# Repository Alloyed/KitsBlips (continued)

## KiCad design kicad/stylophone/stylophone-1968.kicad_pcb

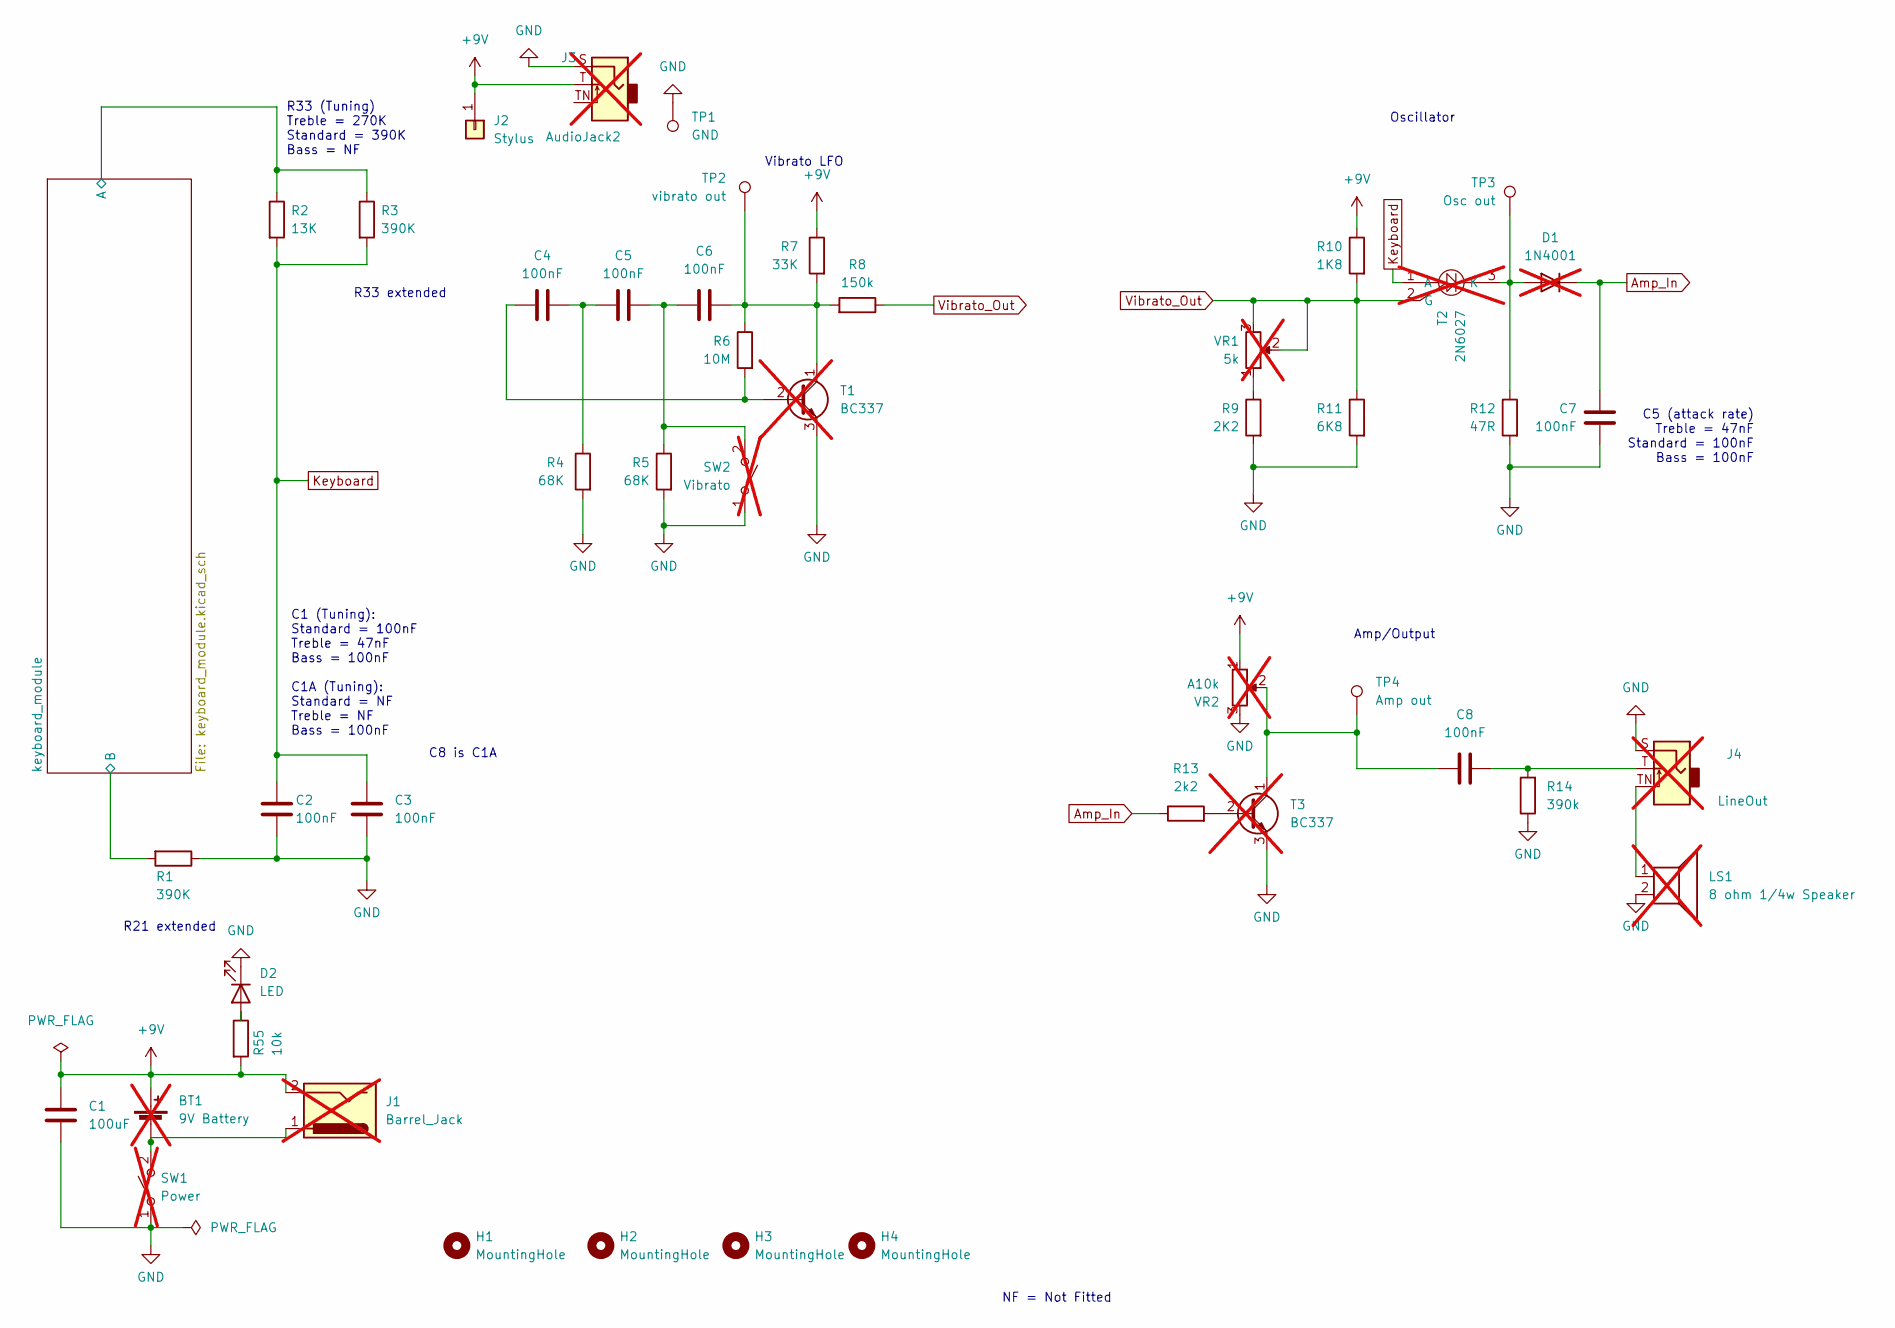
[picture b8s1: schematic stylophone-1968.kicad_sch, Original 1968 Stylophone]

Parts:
BT1: 9V Battery; BatteryHolder_Eagle_12BH611-GR; not fitted
C1: 100uF; C_1206_3216Metric_Pad1.33x1.80mm_HandSolder
C2, C3, C4, C5, C6, C7, C8: 100nF; C_0603_1608Metric_Pad1.08x0.95mm_HandSolder
D1: 1N4001; D_DO-41_SOD81_P10.16mm_Horizontal; not fitted
D2: LED; LED_D3.0mm
H1, H2, H3, H4: MountingHole; MountingHole_3.2mm_M3
J1: Barrel_Jack; BarrelJack_CUI_PJ-063AH_Horizontal; not fitted
J2: Stylus; TestPoint_Pad_D4.0mm
J3: AudioJack2; Jack_3.5mm_QingPu_WQP-PJ398SM_Vertical_CircularHoles; Part Number WQP-WQP518MA; not fitted
J4: LineOut; Jack_3.5mm_QingPu_WQP-PJ398SM_Vertical_CircularHoles; Part Number WQP-WQP518MA; not fitted
LS1: 8 ohm 1/4w Speaker; mouser_speaker; not fitted
R1, R3: 390K; R_0603_1608Metric_Pad0.98x0.95mm_HandSolder
R2: 13K; R_0603_1608Metric_Pad0.98x0.95mm_HandSolder
R4, R5: 68K; R_0603_1608Metric_Pad0.98x0.95mm_HandSolder
R6: 10M; R_0603_1608Metric_Pad0.98x0.95mm_HandSolder
R7: 33K; R_0603_1608Metric_Pad0.98x0.95mm_HandSolder
R8: 150k; R_0603_1608Metric_Pad0.98x0.95mm_HandSolder
R9: 2K2; R_0603_1608Metric_Pad0.98x0.95mm_HandSolder
R10: 1K8; R_0603_1608Metric_Pad0.98x0.95mm_HandSolder
R11: 6K8; R_0603_1608Metric_Pad0.98x0.95mm_HandSolder
R12: 47R; R_0603_1608Metric_Pad0.98x0.95mm_HandSolder
R13: 2k2; R_0603_1608Metric_Pad0.98x0.95mm_HandSolder
R14: 390k; R_0603_1608Metric_Pad0.98x0.95mm_HandSolder
R55: 10k; R_0603_1608Metric_Pad0.98x0.95mm_HandSolder
SW1: Power; SLW-1277744-3A-N-D; not fitted
SW2: Vibrato; SLW-1277744-3A-N-D; not fitted
T1, T3: BC337; TO-92_HandSolder; not fitted
T2: 2N6027; TO-92_HandSolder; not fitted
TP1: GND; TestPoint_Pad_3.0x3.0mm
TP2: vibrato out; TestPoint_Pad_3.0x3.0mm
TP3: Osc out; TestPoint_Pad_3.0x3.0mm
TP4: Amp out; TestPoint_Pad_3.0x3.0mm
VR1: 5k; Potentiometer_Bourns_3266Y_Vertical; not fitted
VR2: A10k; RD901F4015R1B10K00DL1; not fitted

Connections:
+9V: BT1.1 (+), C1.1, J1.2, J2.1, J3.T, R7.1, R10.1, R55.2, VR2.1
/keyboard_module/A1: R2.1, R3.1; also elsewhere on the board
/keyboard_module/B11: R1.2; also elsewhere on the board
Amp_In: C7.1, D1.1 (K), R13.1
GND: C1.2, C2.2, C3.2, C7.2, D2.1 (K), J3.S, J4.S, LS1.2, R1.1, R4.2, R5.2, R9.2, R11.2, R12.2, R14.1, SW1.1 (A), SW2.1 (A), T1.3 (E), T3.3 (E), TP1.1, VR2.3
Keyboard: C2.1, C3.1, R2.2, R3.2, T2.1 (A)
unnamed: BT1.2 (-), J1.1, SW1.2 (B)
unnamed: C4.1, C5.2, R4.1
unnamed: C8.2, J4.T, R14.2
unnamed: D1.2 (A), R12.1, T2.3 (K), TP3.1
unnamed: D2.2 (A), R55.1
unnamed: J4.TN, LS1.1
unnamed: R9.1, VR1.1
unnamed: C5.1, C6.2, R5.1, SW2.2 (B)
unnamed: C4.2, R6.2, T1.2 (B)
unnamed: C6.1, R6.1, R7.2, R8.2, T1.1 (C), TP2.1
unnamed: R13.2, T3.2 (B)
unnamed: C8.1, T3.1 (C), TP4.1, VR2.2
Vibrato_Out: R8.1, R10.2, R11.1, T2.2 (G), VR1.2, VR1.3

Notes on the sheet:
C1 (Tuning): Standard = 100nF Treble = 47nF Bass = 100nF C1A (Tuning): Standard = NF Treble = NF Bass = 100nF
C8 is C1A
Oscillator
R33 extended
R33 (Tuning) Treble = 270K Standard = 390K Bass = NF
R21 extended
Amp/Output
Vibrato LFO
NF = Not Fitted
C5 (attack rate) Treble = 47nF Standard = 100nF Bass = 100nF

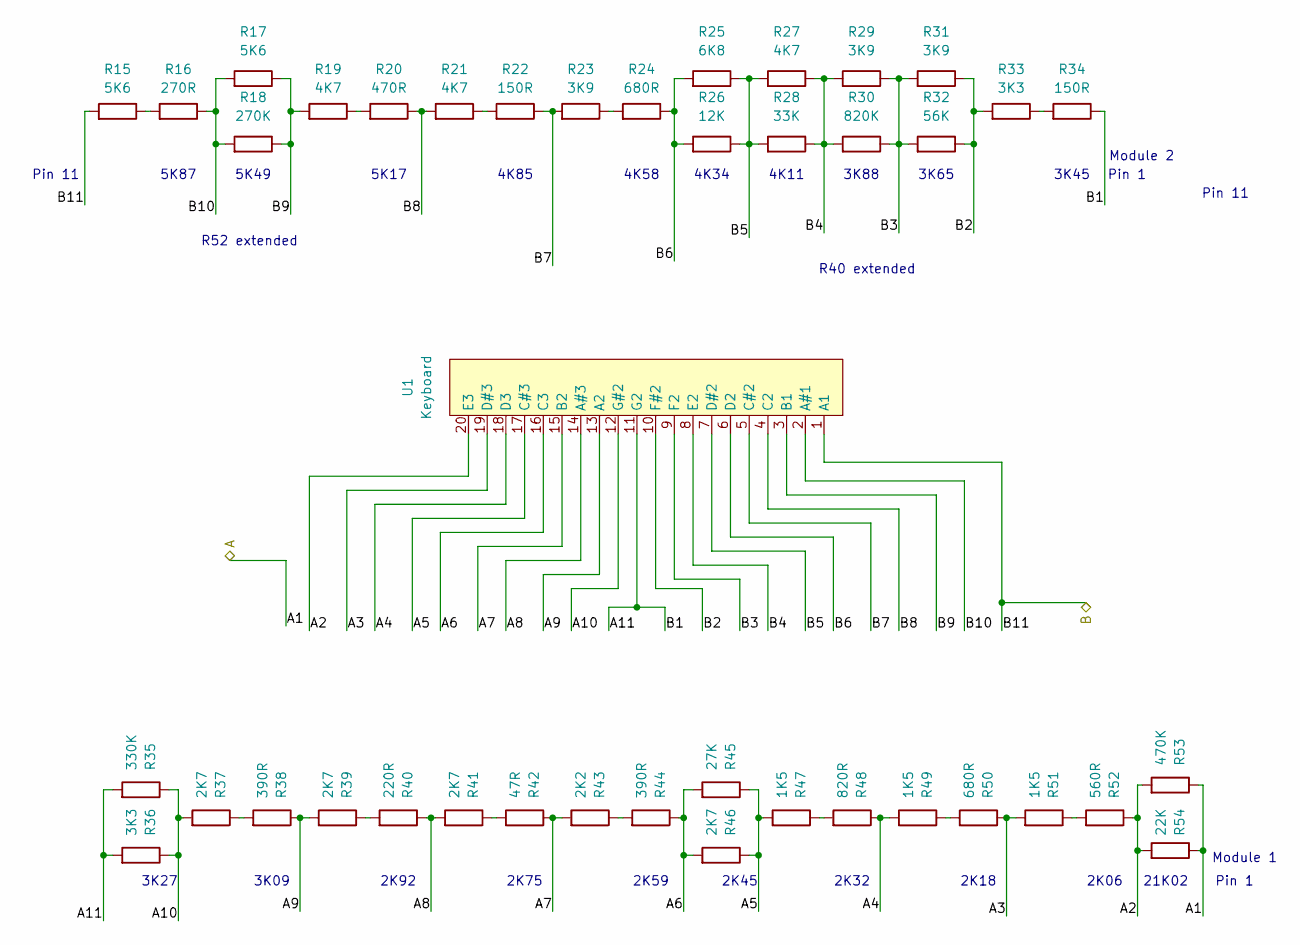
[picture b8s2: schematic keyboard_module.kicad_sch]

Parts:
R15, R17: 5K6; R_0603_1608Metric_Pad0.98x0.95mm_HandSolder
R16: 270R; R_0603_1608Metric_Pad0.98x0.95mm_HandSolder
R18: 270K; R_0603_1608Metric_Pad0.98x0.95mm_HandSolder
R19, R21, R27: 4K7; R_0603_1608Metric_Pad0.98x0.95mm_HandSolder
R20: 470R; R_0603_1608Metric_Pad0.98x0.95mm_HandSolder
R22, R34: 150R; R_0603_1608Metric_Pad0.98x0.95mm_HandSolder
R23, R29, R31: 3K9; R_0603_1608Metric_Pad0.98x0.95mm_HandSolder
R24, R50: 680R; R_0603_1608Metric_Pad0.98x0.95mm_HandSolder
R25: 6K8; R_0603_1608Metric_Pad0.98x0.95mm_HandSolder
R26: 12K; R_0603_1608Metric_Pad0.98x0.95mm_HandSolder
R28: 33K; R_0603_1608Metric_Pad0.98x0.95mm_HandSolder
R30: 820K; R_0603_1608Metric_Pad0.98x0.95mm_HandSolder
R32: 56K; R_0603_1608Metric_Pad0.98x0.95mm_HandSolder
R33, R36: 3K3; R_0603_1608Metric_Pad0.98x0.95mm_HandSolder
R35: 330K; R_0603_1608Metric_Pad0.98x0.95mm_HandSolder
R37, R39, R41, R46: 2K7; R_0603_1608Metric_Pad0.98x0.95mm_HandSolder
R38, R44: 390R; R_0603_1608Metric_Pad0.98x0.95mm_HandSolder
R40: 220R; R_0603_1608Metric_Pad0.98x0.95mm_HandSolder
R42: 47R; R_0603_1608Metric_Pad0.98x0.95mm_HandSolder
R43: 2K2; R_0603_1608Metric_Pad0.98x0.95mm_HandSolder
R45: 27K; R_0603_1608Metric_Pad0.98x0.95mm_HandSolder
R47, R49, R51: 1K5; R_0603_1608Metric_Pad0.98x0.95mm_HandSolder
R48: 820R; R_0603_1608Metric_Pad0.98x0.95mm_HandSolder
R52: 560R; R_0603_1608Metric_Pad0.98x0.95mm_HandSolder
R53: 470K; R_0603_1608Metric_Pad0.98x0.95mm_HandSolder
R54: 22K; R_0603_1608Metric_Pad0.98x0.95mm_HandSolder
U1: Keyboard; stylophone-keyboard

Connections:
/keyboard_module/A1: R53.1, R54.1; also elsewhere on the board
/keyboard_module/A2: R52.1, R53.2, R54.2, U1.20 (E3)
/keyboard_module/A3: R50.1, R51.2, U1.19 (D#3)
/keyboard_module/A4: R48.1, R49.2, U1.18 (D3)
/keyboard_module/A5: R45.1, R46.1, R47.2, U1.17 (C#3)
/keyboard_module/A6: R44.1, R45.2, R46.2, U1.16 (C3)
/keyboard_module/A7: R42.1, R43.2, U1.15 (B2)
/keyboard_module/A8: R40.1, R41.2, U1.14 (A#3)
/keyboard_module/A9: R38.1, R39.2, U1.13 (A2)
/keyboard_module/A10: R35.1, R36.1, R37.2, U1.12 (G#2)
/keyboard_module/A11: R34.1, R35.2, R36.2, U1.11 (G2)
/keyboard_module/B2: R31.1, R32.1, R33.2, U1.10 (F#2)
/keyboard_module/B3: R29.1, R30.1, R31.2, R32.2, U1.9 (F2)
/keyboard_module/B4: R27.1, R28.1, R29.2, R30.2, U1.8 (E2)
/keyboard_module/B5: R25.1, R26.1, R27.2, R28.2, U1.7 (D#2)
/keyboard_module/B6: R24.1, R25.2, R26.2, U1.6 (D2)
/keyboard_module/B7: R22.1, R23.2, U1.5 (C#2)
/keyboard_module/B8: R20.1, R21.2, U1.4 (C2)
/keyboard_module/B9: R17.1, R18.1, R19.2, U1.3 (B1)
/keyboard_module/B10: R16.1, R17.2, R18.2, U1.2 (A#1)
/keyboard_module/B11: R15.2, U1.1 (A1); also elsewhere on the board
unnamed: R15.1, R16.2
unnamed: R19.1, R20.2
unnamed: R21.1, R22.2
unnamed: R23.1, R24.2
unnamed: R33.1, R34.2
unnamed: R37.1, R38.2
unnamed: R39.1, R40.2
unnamed: R41.1, R42.2
unnamed: R43.1, R44.2
unnamed: R47.1, R48.2
unnamed: R49.1, R50.2
unnamed: R51.1, R52.2

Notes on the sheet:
Module 1
4K85
3K65
2K75
R40 extended
5K49
R52 extended
5K17
2K59
Pin 11
2K32
Module 2
Pin 1
3K88
3K45
2K92
4K11
2K45
3K09
2K06
4K58
5K87
4K34
2K18
21K02
3K27

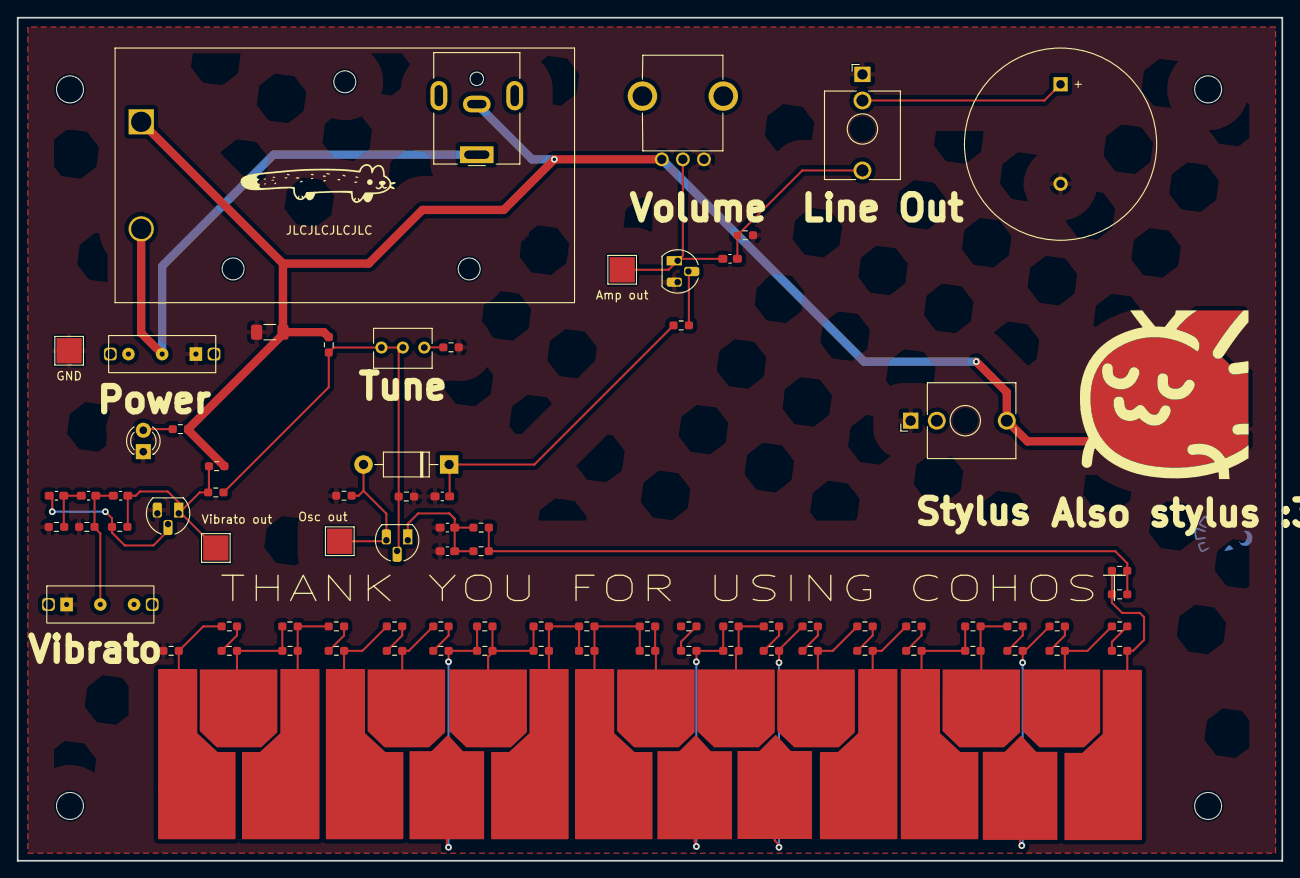
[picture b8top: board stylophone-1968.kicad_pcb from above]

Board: 2 copper layers, 150.0 x 100.0 mm, 87 parts (0 on the bottom side), 50 nets.

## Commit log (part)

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2025-05-20 use static libsdl
2025-05-21 Switch to clapfirst script
2025-05-21 cmake shuffling
2025-05-21 Rewrite plugin.cpp to avoid designated initializers
2025-05-21 more windows fixes
2025-05-21 minor CI speedup by disabling SDL subsystems
2025-05-22 ok that didn't work, try this thing instead
2025-05-23 one of these days
2025-05-24 Fix VCVRack on linux
2025-05-25 Clap: Switch to single-project structure
2025-05-31 build fix
2025-05-31 Start work on effect plugin template
2025-05-31 Stateful extensions, parameters support
2025-06-01 More work to get the parameters extension up to par
2025-06-01 respond to activate/reset events
2025-06-01 fixess from bitwig testing
2025-06-01 Base plugin header cleanup
2025-06-01 Create instrumentPlugin type
2025-06-01 Changes to pass validator testing
2025-06-01 fix clang-tidy warnings
2025-06-01 Create build artifacts for clap plugins
2025-06-01 new clap plugin: sines (test case for instruments)
2025-06-02 oh my god im silly (anyways plugins have sound now)
2025-06-02 gui work
2025-06-04 misc non-gui fixes
2025-06-04 ough
2025-06-05 an alternative to strcpy that's actually portable
2025-06-05 fix windows
2025-06-07 cleanup
2025-06-07 runtime support for multiple apis (for wayland, mostly)
2025-06-07 windows fixes
2025-06-07 SDL multiple-window support
2025-06-07 whoops didn't mean to delete that
2025-06-07 2-way gesture sync
2025-06-07 cleanup, host support logging
2025-06-07 extension support matrix, use SetTimer() on windows (because many hosts don't support the timer api :/)
2025-06-08 support enum parameters. support parameters to text
2025-06-08 cleanup again
2025-06-08 split imgui and sdl into two subclasses
2025-06-08 clap support library now has a name! clapeze (like trapeze, get it)
2025-06-08 event more cleanup
2025-06-08 big refactor: move all processing-related methods and state into "Processor" objects.
2025-06-08 voice allocation
2025-06-13 bweh
2025-06-14 vtable-based polymorphic parameters
2025-06-14 update parameter usage to avoid GetRaw()
2025-06-14 only look for/compile SDL3 if used
2025-06-14 don't define imgui methods if gui not enabled
2025-06-14 oh, duh
2025-06-14 yoloing out a direct translation of crunch
2025-06-14 windows things
2025-06-15 Trying different polyblep algorithm
2025-06-15 smaller things
2025-06-17 CLAP module support (I would call this category or group instead but what can you do)
2025-06-17 tighten up waning options
2025-06-19 auto-format
2025-06-21 initial knob support
2025-06-21 namespacing, some mesh copy-paste
2025-06-22 3d scene exploration
2025-06-22 wip: switch to glad
2025-06-22 Fix clap (by removing gui support)
2025-06-23 ...i still need to play deltarune
2025-06-24 accidentally hyperfocused on building signals from scratch whoops
2025-06-24 it compiles :)
2025-06-27 fun with untested dsp code :)
2025-06-29 more gfx, created stub for sprite batches
2025-06-29 name the thing what it is
2025-07-03 switchting to magnum graphics lib
2025-07-03 scene from sample player ported
2025-07-04 header cleanup
2025-07-04 actual test code :0
2025-07-04 ai slop cleanup (watchout!)
2025-07-04 windows testing
2025-07-05 clap fixes
2025-07-05 disabling clap macos for now
2025-07-08 corrade logging banished, kitgui::log in
2025-07-08 proper window resizing
2025-07-08 /shrug
2025-07-12 re-enable debug imgui support
2025-07-13 platform timer
2025-07-20 move clapeze into a top-level subdirectory
2025-07-20 compile windows again
2025-07-21 big refactor: rename Exts to "features", adopt "TObject" prefix for template params
2025-07-21 update clap plugins to use param traits
2025-07-22 move more param configuration into the trait
2025-07-22 clang-tidy
2025-07-22 clang-tidy changes for kitdsp
2025-08-03 more cleanup
2025-08-05 fix compiler warnings
2025-08-05 re-enable clap macos
2025-08-08 remove GLAD. add AudioFile (for wav file reading/writing)
2025-08-08 Fixup test for chorus (yeah it's broken...)
2025-08-08 chorus works now :)
2025-08-09 move more tests to AudioFile
2025-08-09 playing with an eventide h910 algorithm (this isn't a grain player, whoops~~~)
2025-08-10 actually name the harmonizer what it is
2025-08-15 frequency shifter works :0
2025-08-15 fix windows builds
2025-08-24 move sdl implementation into a impl class
2025-08-24 inline old platform code into the one SDL file to rule them all
2025-08-24 update clap wrapper for new gui api
2025-08-24 rendering.... works....?
2025-08-24 don't include SDL3 when we don't need to
2025-08-25 wide string shenanigans
2025-08-25 crunch gui seems to work!
2025-08-25 okkkk one more
2025-08-28 Add skeletons for new daw plugins
2025-08-29 ok what if i added every plugin all at once
2025-08-29 small sync
2025-08-30 fill out each plugin with debug gui
2025-08-31 linux fixups
2025-08-31 fixups 2
2025-08-31 fixups 3
2025-09-04 shuffling things around for no particular reason
2025-09-04 Split out extensions and features for good: now each feature can register as many extensions as it likes (or none!)
2025-09-06 Add skeleton of preset support
2025-09-07 feature frenzy
2025-09-16 tmp: working out affinity designer -> vcv rack pipeline
2025-09-16 I forgor
2025-09-17 fix macosx build?
2025-09-17 MacOS fix, switch to libfmt instead of std::format
2025-09-17 use builtin fmt library. silly.
2025-09-17 fix windows pls :pleading:
2025-09-28 windows fix (again)
2025-09-28 cache is dependent on repo state, duh
2025-09-28 Add cocoa stub implementation
2025-09-28 cmake: try out composite actions
2025-09-28 fix macos :)
2025-09-28 more ci cleanup
2025-12-28 ummmm, i don't remember :(
2025-12-31 use automatic entry point in actual clap plugins
2025-12-31 3d still needs time to bake
2025-12-31 kitgui: file loading infrastructure so i can skippo the C++ embedded thing
2025-12-31 entry point fixes
2025-12-31 more buildfix
2025-12-31 add more examples
2025-12-31 fix 3d scene loading for actual
2026-01-04 Fix annoying ParamTraits template bug
    ParamTraits<Param1::myId> and ParamTraits<Param2::myId> both eventually
    resolve to ParamTraits<1>, even if the params are enum classes. to fix,
    we'll manually pass in the full params enum as a qualifier
2026-01-04 plugin entry callsite simplification
2026-01-05 Expose gfx/Scene as a non dom type/api
2026-01-05 kitskeys panel first pass, CI fixes
2026-01-05 yes i know im using a nonstandard extension
2026-01-06 robustify linux/x11 implementation (so i can hunt down the issue a bit better)
2026-01-06 keysynth parameter cleanup
2026-01-06 combined voice pool; modulation storage
2026-01-06 Fix linux gui!!!!
2026-01-07 redo file loader plumbing. (untested but this should mean physfs in gui will Just Work)
2026-01-07 Fix context cleanup: app should always be destroyed before rest of context
2026-01-07 fix ci maybe
2026-01-07 Fix embarassing C++ bugs
2026-01-07 ok this one is more embarassing for apple
2026-01-08 lotsa small stuff
2026-01-09 lotsa big stuff
2026-01-10 fix mac?
2026-01-11 big documentation pass
2026-01-11 add pugl to sdk dir
2026-01-12 Fully replace physfs with miniz
2026-01-12 update docs
2026-01-13 pugl, big implementation pass
2026-01-13 pugl bugfixes
2026-01-14 fix debug ui bug
2026-01-14 ci fixes
2026-01-14 mac fixes
2026-01-14 oops that makes sense
2026-01-16 wrenching on cmake a bit
2026-01-16 format_to_n doesn't write the terminator :(
2026-01-17 optional sentry.io crash reporting
2026-01-18 sentry doubled the build size, turning off for now
2026-01-18 also mac
2026-01-22 rename clap folder to daw
2026-01-23 unit tests, woah
2026-01-24 mock host for convenient testing
2026-01-24 docs pass
2026-01-24 new experiment: alternate parameter implementations
2026-01-24 adopt new parameter system in clapeze
2026-01-24 upgrade daw to use new parameter system too
2026-01-24 constraints and concepts (scary!)
2026-01-24 remove vestigial clapeze::params::Id type
2026-01-24 more and better integration testing
2026-01-25 exploring toml serialization
2026-01-25 iostreams for clap streams
2026-01-25 perf and time tracking
2026-01-25 Support UI scale on SDL backend, fixes X11 being tiny
2026-01-26 stuff
2026-01-28 update libdaisy
2026-01-28 update other submodules
2026-01-28 update vcvrack sdk
2026-01-28 add gltfpack and basisu for asset packing
2026-01-28 daisy fix
2026-01-28 verbose logs
2026-01-28 silly mistake: .gitignore ignored the binaries :p
2026-01-28 initial setup script
2026-01-28 add sentry to ci
2026-01-29 AI statement (gee i wonder what prompted this)
2026-01-30 whoops unitialized memory!!
2026-01-31 gui backend hardening
2026-01-31 actually working knobs (WOAH)
2026-02-01 bugfix pass: fix dangling pointers resulting from not realizing the host is allowed to pass multiple host pointers back, and a multi-window imgui thing
2026-02-03 KitsKeys Chord mode
2026-02-03 fixed polyphonic voice stealing algo
2026-02-03 lots of poorly considered stuff
2026-02-03 silly mistake: putting windows inside of windows are we
2026-02-03 toggle switches
2026-02-04 ui cleanup
2026-02-07 better oversampling
2026-02-07 misc cleanup
2026-02-08 nvm ill bring back lfo sync later, more issues than expected
2026-02-08 new kitskeys front panel
2026-02-08 LFO sync + LFO out(for light)
2026-02-08 scene hierarchy debug view, bounding-box knobs
2026-02-08 add sentry-cli to cmake
2026-02-09 x11 highdpi hack
2026-02-10 Big params refactor (split up FillInformation, add key, deemphasize module as it's relatively unused)
2026-02-11 key followup, updating callsites and such
2026-02-11 warning silencer
2026-02-13 big filename refactor
2026-02-13 file renaming: group audio stuff together under "processor" folder
2026-02-13 include clapeze with system headers when external to it
2026-02-14 un-templatify params handle storage
2026-02-14 custom casts
2026-02-15 exposing ambient brightness
2026-02-15 you should be pulling in assets if you use kitgui
2026-02-15 pawing at preset browser
2026-02-15 preset work
2026-02-16 remove glob, use no-compression mode for zip bundle
2026-02-16 ok nvm i'll write my own zip-creator
2026-02-20 wip: post processing pass
2026-02-21 emissive blur effect!
2026-02-21 more light tricks
2026-02-21 whoops
2026-02-22 new model
2026-02-22 toggle off basis for now
2026-02-22 glb test assets
2026-02-23 asset
2026-02-23 emissive effect tweaking
2026-02-27 wawa
2026-02-28 Fix #29 and #30
2026-03-03 fix #32: don't try to set the current dpi awareness setting, you and the host may disagree!
2026-03-06 KitsBlips DAW version 0.1.0
2026-04-13 snapshot testing... maybe
2026-04-13 rename ProcessorHandle to AudioHandle
2026-04-13 snapshots!
2026-04-21 implement it
2026-04-22 going psola-mode
2026-04-26 more pitch shift groundwork
2026-05-02 ...i forget
2026-05-03 disperser (?) ...i may have screwed up the math i think
2026-05-07 disperser work, crossover filter, simd vector (experimental)
2026-05-07 filter plugin
2026-05-07 transfer functions (for later)
2026-05-08 fix a few kitsblips bugs
2026-05-09 filter fixies
2026-05-09 buildfix
2026-05-17 starting on layersynth
2026-05-17 added "some stuff"
2026-05-18 swagify
2026-05-20 3 band equalizer
2026-05-22 crazy work (normal work)
2026-05-22 more wiring
2026-05-22 slowly running out of awake juice
2026-05-23 event based parameters?
2026-05-23 nativefiledialog integration
2026-05-23 more things working
2026-05-23 weewa
2026-05-23 ok this is mostly crash free now i think
2026-05-23 more fixies
2026-05-23 ci upgrade
2026-05-24 fix parameter queue getting overfull as a result of initialization
2026-05-24 polyphonic modulation (maybe)
2026-05-24 switch to drwav/drflac for sample loading (that means flac support, yipee)
2026-05-24 fixing again
2026-05-24 killing sentry
2026-05-24 modulation works now
2026-05-25 Jam Session :)
2026-05-31 sample player debugging
2026-05-31 update snapshots
2026-06-02 fix everything, all at once (again, whoops)
2026-06-04 sample player polish
2026-06-04 more sample player api polish
2026-06-05 add implot
2026-06-05 dx7 envelope (probably better to name multistage?)
2026-06-05 fantsy sample editor
2026-06-06 lofi sample pre-processing
2026-06-07 unnecessarily big cl
2026-06-07 fix preset bugs
2026-06-07 filter envelope, actually expose pitch lfo mult
2026-06-09 maybe...
2026-06-14 some stuff....
2026-06-15 preset browser fleshing out
2026-06-16 beginnings of singer module
2026-06-16 singer midi support
2026-06-21 ci fix
